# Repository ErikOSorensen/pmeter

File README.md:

# pmeter
RF power meter (AD8307 based) -- software to run on Raspberry Pi.

The power meter has a separate module with the sensor, and the plan is
to use an ADS1115, attached to a Raspberry Pi pico by i2c to sense the
voltage emitted (which will be more or less an affine function of the
power applied at the sensor. According to the [Analog Devices
datasheet](http://www.analog.com/media/en/technical-documentation/data-sheets/AD8307.pdf)
it should be possible to get decent performance from -75dBm to +17dBm
in the range from DC to 500MHz, but -70 to +10 dBm from DC to 150 MHz should
be achievable. There is a ADS1115 micropython library here: https://github.com/robert-hh/ads1x15

I want a controller housing with ports for two sensor heads. The sensor heads
will be built into aluminium diecast enclosure with RF connectors on one end and
a 4-wire cable to the controller unit: 1) power, 2) GND, 3) output voltage from
sensor, and 4) a voltage that signals which sensor head this is to the controller.

I want a raspberry pi pico with a wiznet 5500 ethernet controller, such that I
can use a REST interface to fetch readings if I like to. I also want an
interactive use. For interactive use I need to 1) be able to set the frequency
(calibrarion constants), offsets, and maybe the display units (from dBm to
Volts?). A rotary controller with a  button should be enough to step through
four modes: Channel A frequency, A offset, A units, B frequency, B offset, B
units. Then a display: Two lines of a 16x2 LCD display should in principle be
enough. Alternative: One 0.96 inch display for each channel (these are i2c). I
probably also should be able to display the ip-address of the controller (if
any).

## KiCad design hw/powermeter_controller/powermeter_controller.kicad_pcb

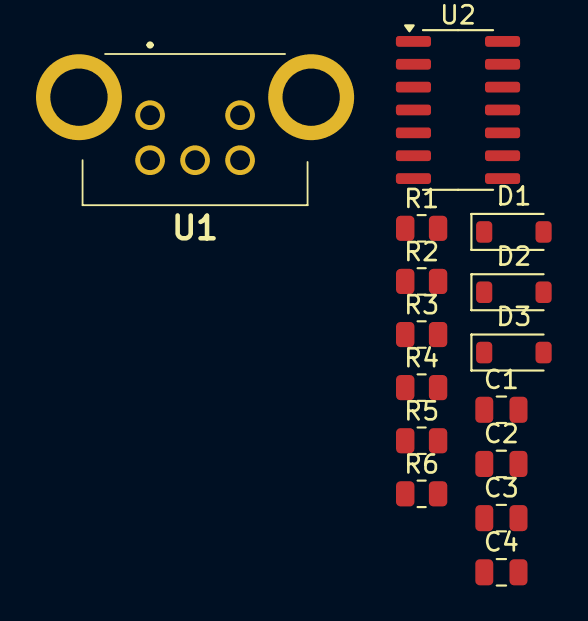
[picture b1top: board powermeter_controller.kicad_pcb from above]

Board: 2 copper layers, 15 parts (0 on the bottom side), 8 nets, no tracks yet.

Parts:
C1, C2, C3, C4: 100n; C_0805_2012Metric
D1, D2, D3: 1n4148; D_SOD-123
R1, R2, R3: 18k; R_0805_2012Metric
R4, R5, R6: 82k; R_0805_2012Metric
U1: PEC12R-2217F-S0024; PEC12R2217FS0024
U2: 74HC14; SOIC-14_3.9x8.7mm_P1.27mm

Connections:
+3.3V: C4.2, R4.2, R5.2, R6.1, U2.14 (VCC)
GND: C1.2, C2.2, C3.2, C4.1, U1.2, U1.C1 (COMMON), U1.MH1, U1.MH2, U2.7 (GND)
unnamed: D1.2 (A), R1.2, R6.2, U1.1
unnamed: C1.1, D1.1 (K), R1.1, U2.1
unnamed: D2.2 (A), R2.1, R5.1, U1.A1 (CHANNEL_A)
unnamed: C2.1, D2.1 (K), R2.2, U2.3
unnamed: D3.2 (A), R3.1, R4.1, U1.B1 (CHANNEL_B)
unnamed: C3.1, D3.1 (K), R3.2, U2.5

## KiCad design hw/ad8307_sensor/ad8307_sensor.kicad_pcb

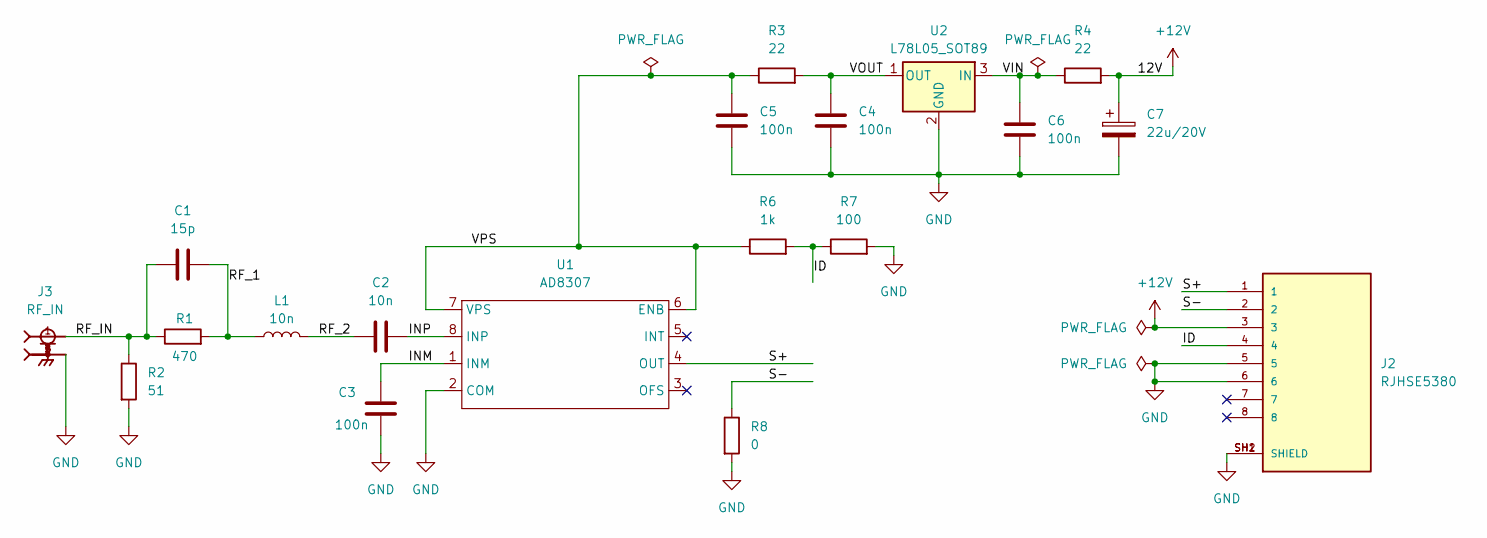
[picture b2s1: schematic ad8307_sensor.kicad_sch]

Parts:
C1: 15p; C_0603_1608Metric
C2: 10n; C_0603_1608Metric
C3: 100n; C_0603_1608Metric
C4, C5, C6: 100n; C_0805_2012Metric
C7: 22u/20V; CP_EIA-3528-21_Kemet-B
J2: RJHSE5380; AMPHENOL_RJHSE5380; PARTREV B
J3: RF_IN; SAMTEC_SMA-J-P-X-RA-TH1; PARTREV K
L1: 10n; L_0603_1608Metric
R1: 470; R_0603_1608Metric
R2: 51; R_0603_1608Metric
R3, R4: 22; R_0805_2012Metric
R6: 1k; R_0805_2012Metric
R7: 100; R_0805_2012Metric
R8: 0; R_0805_2012Metric
U1: AD8307; SOIC-8_3.9x4.9mm_P1.27mm
U2: L78L05_SOT89; SOT-89-3

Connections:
+12V: C7.1, J2.3, R4.2
/ID: J2.4, R6.2, R7.1
/INM: C3.1, U1.1 (INM)
/INP: C2.2, U1.8 (INP)
/RF_1: C1.2, L1.1, R1.2
/RF_2: C2.1, L1.2
/RF_IN: C1.1, J3.1, R1.1, R2.1
/S+: J2.1, U1.4 (OUT)
/S-: J2.2, R8.1
/VIN: C6.1, R4.1, U2.3 (IN)
/VOUT: C4.1, R3.2, U2.1 (OUT)
/VPS: C5.1, R3.1, R6.1, U1.6 (ENB), U1.7 (VPS)
GND: C3.2, C4.2, C5.2, C6.2, C7.2, J2.5, J2.6, J2.SH1 (SHIELD), J2.SH2 (SHIELD), J3.2, J3.3, J3.4, J3.5, R2.2, R7.2, R8.2, U1.2 (COM), U2.2 (GND)

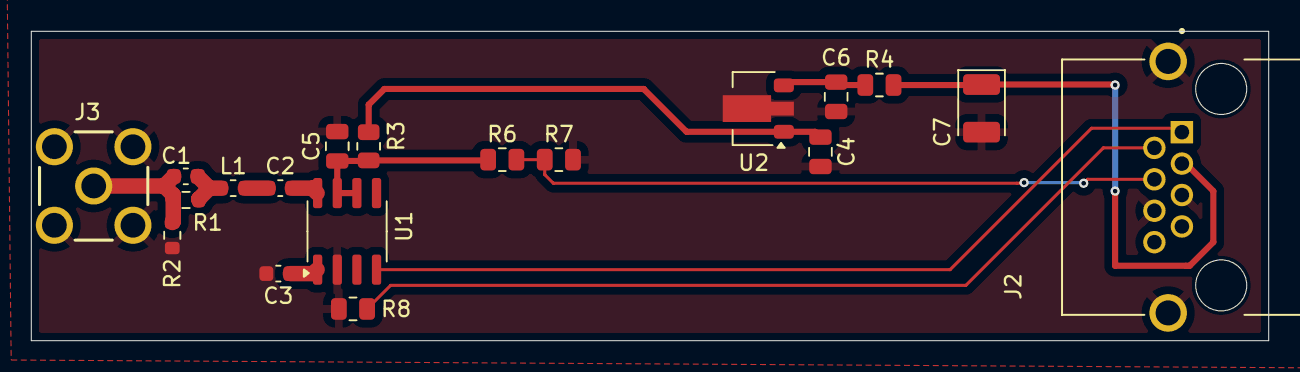
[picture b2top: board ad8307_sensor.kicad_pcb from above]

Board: 2 copper layers, 80.0 x 20.0 mm, 19 parts (0 on the bottom side), 13 nets.

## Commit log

2017-12-29 Beginning a description.
2017-12-29 Fixed typo in markdown syntax.
2025-04-14 new ideas.
2025-04-18 Laying out a sensor to fit in a 80x25x25mm box with RJ45 connection to the controller box.
2025-04-20 Starting schematics of controller.
2025-05-10 symtable
